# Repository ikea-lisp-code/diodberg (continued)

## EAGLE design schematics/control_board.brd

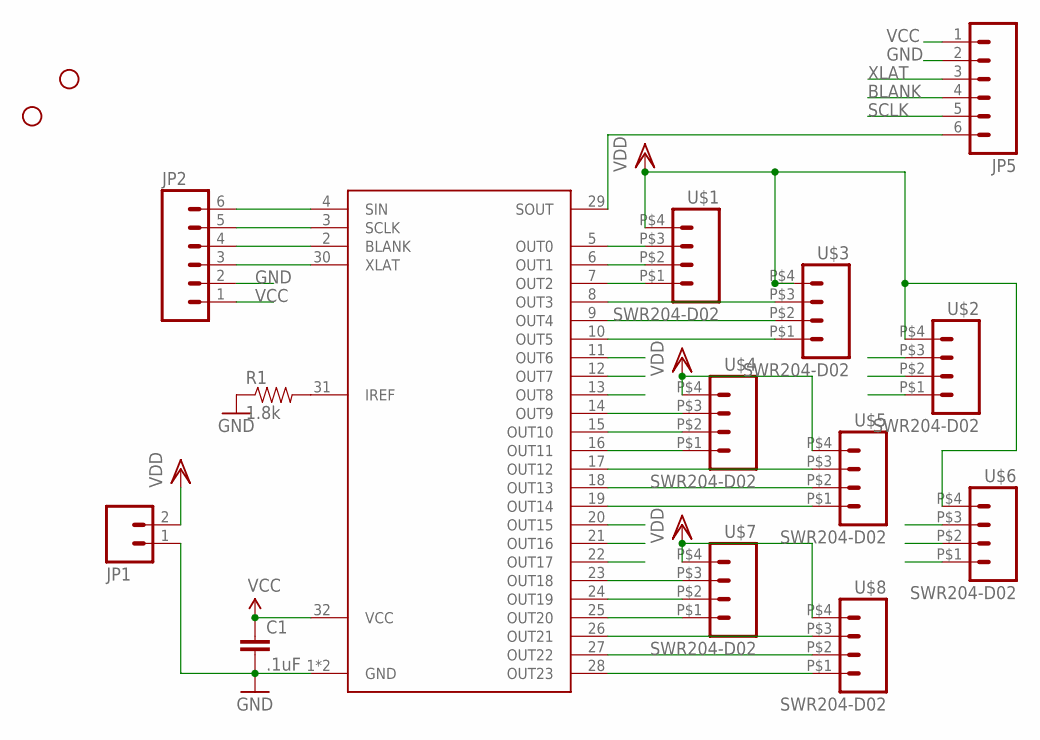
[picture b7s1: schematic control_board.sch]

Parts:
C1: .1uF; 0603-CAP
JP1: M02-JST-2MM-SMT; JST-2-SMD
JP2, JP5: M06LOCK; 1X06_LOCK
R1: 1.8k; 0603-RES
STANDOFF2, STANDOFF3: STAND-OFF
TLC5947: TLC5947DAP; DAP
U$1, U$2, U$3, U$4, U$5, U$6, U$7, U$8: SWR204-D02; SWR204

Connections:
BLANK: JP2.4, JP5.4, TLC5947.2 (BLANK)
GND: C1.2, JP1.1 (2), JP2.2, JP5.2, R1.1, TLC5947.1 (GND), TLC5947.GND
unnamed: R1.2, TLC5947.31 (IREF)
OUT0: TLC5947.5 (OUT0), U$1.P$3 (3)
OUT1: TLC5947.6 (OUT1), U$1.P$2 (2)
OUT2: TLC5947.7 (OUT2), U$1.P$1 (1)
OUT3: TLC5947.8 (OUT3), U$3.P$3 (3)
OUT4: TLC5947.9 (OUT4), U$3.P$2 (2)
OUT5: TLC5947.10 (OUT5), U$3.P$1 (1)
OUT6: TLC5947.11 (OUT6), U$2.P$3 (3)
OUT7: TLC5947.12 (OUT7), U$2.P$2 (2)
OUT8: TLC5947.13 (OUT8), U$2.P$1 (1)
OUT9: TLC5947.14 (OUT9), U$4.P$3 (3)
OUT10: TLC5947.15 (OUT10), U$4.P$2 (2)
OUT11: TLC5947.16 (OUT11), U$4.P$1 (1)
OUT12: TLC5947.17 (OUT12), U$5.P$3 (3)
OUT13: TLC5947.18 (OUT13), U$5.P$2 (2)
OUT14: TLC5947.19 (OUT14), U$5.P$1 (1)
OUT15: TLC5947.20 (OUT15), U$6.P$3 (3)
OUT16: TLC5947.21 (OUT16), U$6.P$2 (2)
OUT17: TLC5947.22 (OUT17), U$6.P$1 (1)
OUT18: TLC5947.23 (OUT18), U$7.P$3 (3)
OUT19: TLC5947.24 (OUT19), U$7.P$2 (2)
OUT20: TLC5947.25 (OUT20), U$7.P$1 (1)
OUT21: TLC5947.26 (OUT21), U$8.P$3 (3)
OUT22: TLC5947.27 (OUT22), U$8.P$2 (2)
OUT23: TLC5947.28 (OUT23), U$8.P$1 (1)
SCLK: JP2.5, JP5.5, TLC5947.3 (SCLK)
SIN: JP2.6, TLC5947.4 (SIN)
SOUT: JP5.6, TLC5947.29 (SOUT)
VCC: C1.1, JP2.1, JP5.1, TLC5947.32 (VCC)
VDD: JP1.2 (1), U$1.P$4 (4), U$2.P$4 (4), U$3.P$4 (4), U$4.P$4 (4), U$5.P$4 (4), U$6.P$4 (4), U$7.P$4 (4), U$8.P$4 (4)
XLAT: JP2.3, JP5.3, TLC5947.30 (XLAT)

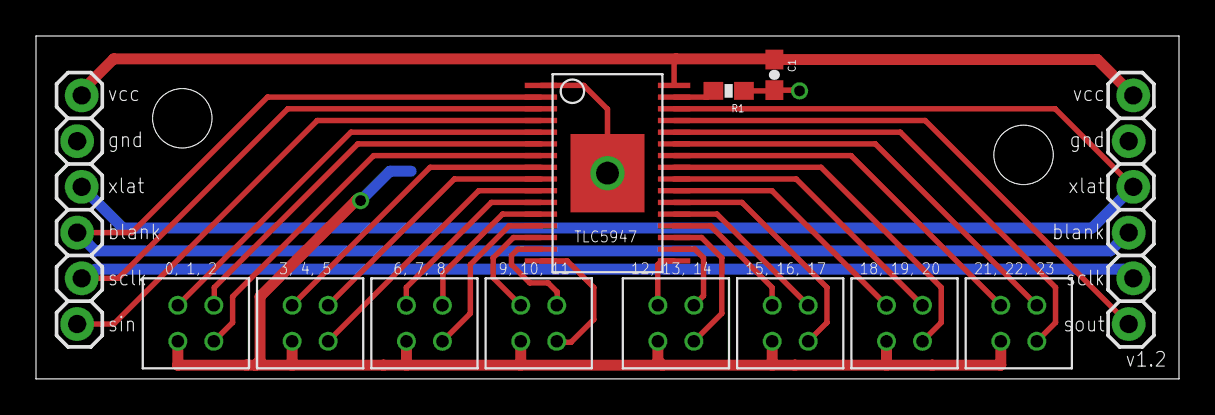
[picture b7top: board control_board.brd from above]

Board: 2 copper layers, 63.5 x 19.1 mm, 16 parts (1 on the bottom side), 33 nets.

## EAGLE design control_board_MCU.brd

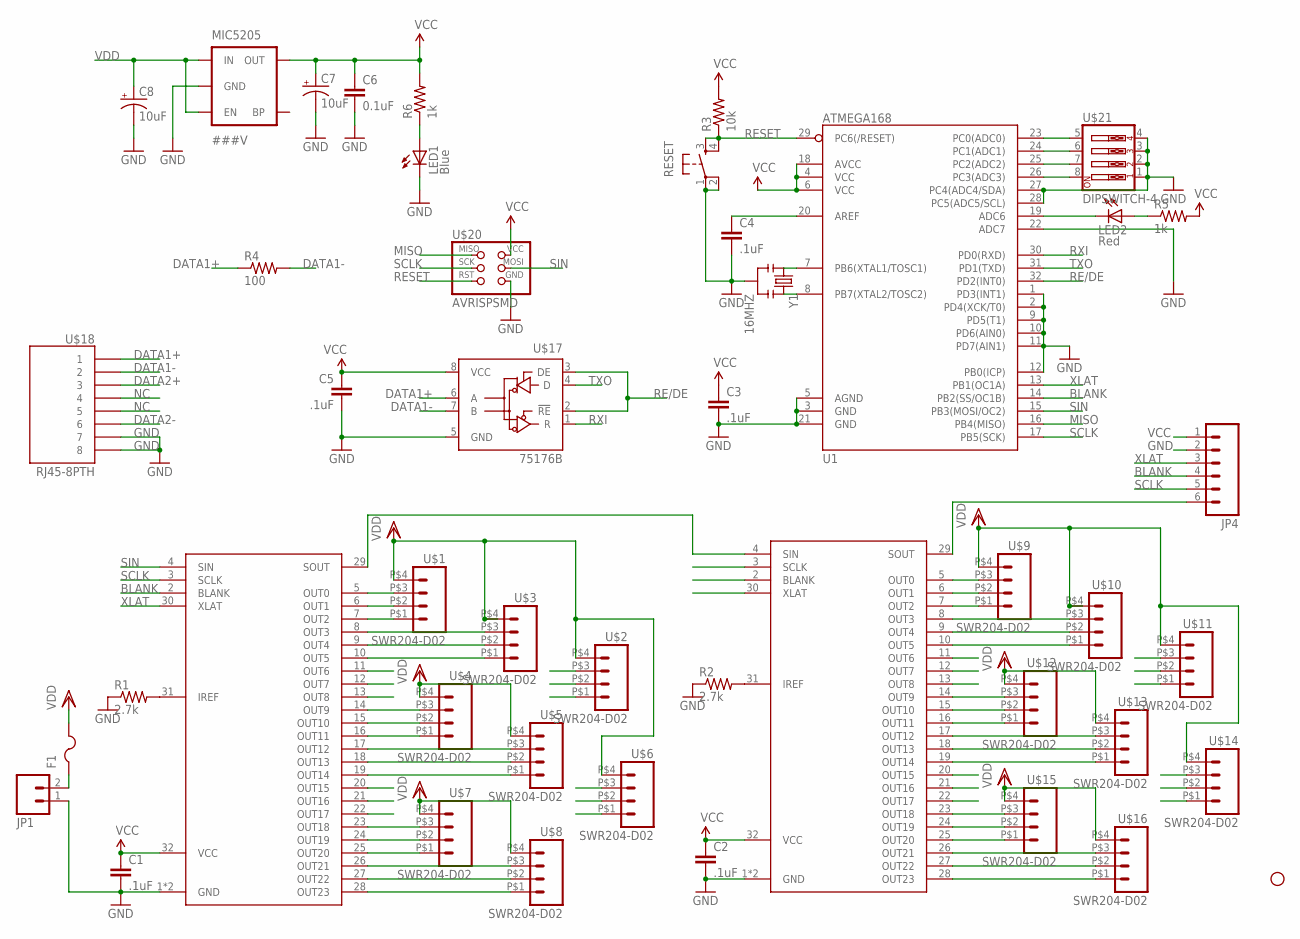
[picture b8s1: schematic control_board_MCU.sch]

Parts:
C1, C2, C3, C4, C5: .1uF; 0402-CAP
C6: 0.1uF; 0402-CAP
C7, C8: 10uF; EIA3216
F1: PTCFUSE-1812; 1812
JP1: M02-JST-2MM-SMT; JST-2-SMD
JP4: M06LOCK; 1X06_LOCK
LED1: Blue; LED-0603
LED2: Red; LED-0603
MIC5205: ###V; SOT23-5
R1, R2: 2.7k; 0603-RES
R3: 10k; 0402-RES
R4: 100; 1206
R5, R6: 1k; C0402
RESET: TAC_SWITCHSMD; TACTILE_SWITCH_SMD
STANDOFF1: STAND-OFF
TLC5947, TLC5947-2: TLC5947DAP; DAP
U1: ATMEGA168; TQFP32-08
U$1, U$2, U$3, U$4, U$5, U$6, U$7, U$8, U$9, U$10, U$11, U$12, U$13, U$14, U$15, U$16: SWR204-D02; SWR204
U$17: 75176B; D_R-PDSO-G8
U$18: RJ45-8PTH; RJ45-8
U$20: AVRISPSMD; 2X03SMD
U$21: DIPSWITCH-4; DIPSWITCH-04
Y1: 16MHZ; RESONATOR-SMD

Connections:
BLANK: JP4.4, TLC5947.2 (BLANK), TLC5947-2.2 (BLANK), U1.14 (PB2(SS/OC1B))
DATA1+: R4.1, U$17.6 (A), U$18.1
DATA1-: R4.2, U$17.7 (B), U$18.2
DATA2+: U$18.3
DATA2-: U$18.6
GND: C1.2, C2.2, C3.2, C4.2, C5.2, C6.2, C7.C (-), C8.C (-), JP1.1 (2), JP4.2, LED1.C, MIC5205.2 (GND), R1.1, R2.1, RESET.1, RESET.2, TLC5947.1 (GND), TLC5947.GND, TLC5947-2.1 (GND), TLC5947-2.GND, U1.1 (PD3(INT1)), U1.2 (PD4(XCK/T0)), U1.3 (GND), U1.5 (AGND), U1.9 (PD5(T1)), U1.10 (PD6(AIN0)), U1.11 (PD7(AIN1)), U1.12 (PB0(ICP)), U1.21 (GND), U1.22 (ADC7), U1.27 (PC4(ADC4/SDA)), U1.28 (PC5(ADC5/SCL)), U$17.5 (GND), U$18.7, U$18.8, U$20.6 (GND), U$21.1, U$21.2, U$21.3, U$21.4, Y1.2
MISO: U1.16 (PB4(MISO)), U$20.1 (MISO)
unnamed: R1.2, TLC5947.31 (IREF)
unnamed: R2.2, TLC5947-2.31 (IREF)
unnamed: C4.1, U1.20 (AREF)
unnamed: U1.7 (PB6(XTAL1/TOSC1)), Y1.1
unnamed: U1.8 (PB7(XTAL2/TOSC2)), Y1.3
unnamed: LED2.C, U1.19 (ADC6)
unnamed: LED2.A, R5.1
unnamed: F1.1, JP1.2 (1)
unnamed: U1.23 (PC0(ADC0)), U$21.5
unnamed: U1.24 (PC1(ADC1)), U$21.6
unnamed: U1.25 (PC2(ADC2)), U$21.7
unnamed: U1.26 (PC3(ADC3)), U$21.8
unnamed: LED1.A, R6.1
NC: U$18.4, U$18.5
OUT0: TLC5947.5 (OUT0), U$1.P$3 (3)
OUT1: TLC5947.6 (OUT1), U$1.P$2 (2)
OUT2: TLC5947.7 (OUT2), U$1.P$1 (1)
OUT3: TLC5947.8 (OUT3), U$3.P$3 (3)
OUT4: TLC5947.9 (OUT4), U$3.P$2 (2)
OUT5: TLC5947.10 (OUT5), U$3.P$1 (1)
OUT6: TLC5947.11 (OUT6), U$2.P$3 (3)
OUT7: TLC5947.12 (OUT7), U$2.P$2 (2)
OUT8: TLC5947.13 (OUT8), U$2.P$1 (1)
OUT9: TLC5947.14 (OUT9), U$4.P$3 (3)
OUT10: TLC5947.15 (OUT10), U$4.P$2 (2)
OUT11: TLC5947.16 (OUT11), U$4.P$1 (1)
OUT12: TLC5947.17 (OUT12), U$5.P$3 (3)
OUT13: TLC5947.18 (OUT13), U$5.P$2 (2)
OUT14: TLC5947.19 (OUT14), U$5.P$1 (1)
OUT15: TLC5947.20 (OUT15), U$6.P$3 (3)
OUT16: TLC5947.21 (OUT16), U$6.P$2 (2)
OUT17: TLC5947.22 (OUT17), U$6.P$1 (1)
OUT18: TLC5947.23 (OUT18), U$7.P$3 (3)
OUT19: TLC5947.24 (OUT19), U$7.P$2 (2)
OUT20: TLC5947.25 (OUT20), U$7.P$1 (1)
OUT21: TLC5947.26 (OUT21), U$8.P$3 (3)
OUT22: TLC5947.27 (OUT22), U$8.P$2 (2)
OUT23: TLC5947.28 (OUT23), U$8.P$1 (1)
OUT24: TLC5947-2.5 (OUT0), U$9.P$3 (3)
OUT25: TLC5947-2.6 (OUT1), U$9.P$2 (2)
OUT26: TLC5947-2.7 (OUT2), U$9.P$1 (1)
OUT27: TLC5947-2.8 (OUT3), U$10.P$3 (3)
OUT28: TLC5947-2.9 (OUT4), U$10.P$2 (2)
OUT29: TLC5947-2.10 (OUT5), U$10.P$1 (1)
OUT30: TLC5947-2.11 (OUT6), U$11.P$3 (3)
OUT31: TLC5947-2.12 (OUT7), U$11.P$2 (2)
OUT32: TLC5947-2.13 (OUT8), U$11.P$1 (1)
OUT33: TLC5947-2.14 (OUT9), U$12.P$3 (3)
OUT34: TLC5947-2.15 (OUT10), U$12.P$2 (2)
OUT35: TLC5947-2.16 (OUT11), U$12.P$1 (1)
OUT36: TLC5947-2.17 (OUT12), U$13.P$3 (3)
OUT37: TLC5947-2.18 (OUT13), U$13.P$2 (2)
OUT38: TLC5947-2.19 (OUT14), U$13.P$1 (1)
OUT39: TLC5947-2.20 (OUT15), U$14.P$3 (3)
OUT40: TLC5947-2.21 (OUT16), U$14.P$2 (2)
OUT41: TLC5947-2.22 (OUT17), U$14.P$1 (1)
OUT42: TLC5947-2.23 (OUT18), U$15.P$3 (3)
OUT43: TLC5947-2.24 (OUT19), U$15.P$2 (2)
OUT44: TLC5947-2.25 (OUT20), U$15.P$1 (1)
OUT45: TLC5947-2.26 (OUT21), U$16.P$3 (3)
OUT46: TLC5947-2.27 (OUT22), U$16.P$2 (2)
OUT47: TLC5947-2.28 (OUT23), U$16.P$1 (1)
RE/DE: U1.32 (PD2(INT0)), U$17.2 (!RE), U$17.3 (DE)
RESET: R3.1, RESET.3, RESET.4, U1.29 (PC6(/RESET)), U$20.5 (RST)
RXI: U1.30 (PD0(RXD)), U$17.1 (R)
SCLK: JP4.5, TLC5947.3 (SCLK), TLC5947-2.3 (SCLK), U1.17 (PB5(SCK)), U$20.3 (SCK)
SIN: TLC5947.4 (SIN), U1.15 (PB3(MOSI/OC2)), U$20.4 (MOSI)
SOUT: TLC5947.29 (SOUT), TLC5947-2.4 (SIN)
SOUT1: JP4.6, TLC5947-2.29 (SOUT)
TXO: U1.31 (PD1(TXD)), U$17.4 (D)
VCC: C1.1, C2.1, C3.1, C5.1, C6.1, C7.A (+), JP4.1, MIC5205.5 (OUT), R3.2, R5.2, R6.2, TLC5947.32 (VCC), TLC5947-2.32 (VCC), U1.4 (VCC), U1.6 (VCC), U1.18 (AVCC), U$17.8 (VCC), U$20.2 (VCC)
VDD: C8.A (+), F1.2, MIC5205.1 (IN), MIC5205.3 (EN), U$1.P$4 (4), U$2.P$4 (4), U$3.P$4 (4), U$4.P$4 (4), U$5.P$4 (4), U$6.P$4 (4), U$7.P$4 (4), U$8.P$4 (4), U$9.P$4 (4), U$10.P$4 (4), U$11.P$4 (4), U$12.P$4 (4), U$13.P$4 (4), U$14.P$4 (4), U$15.P$4 (4), U$16.P$4 (4)
XLAT: JP4.3, TLC5947.30 (XLAT), TLC5947-2.30 (XLAT), U1.13 (PB1(OC1A))

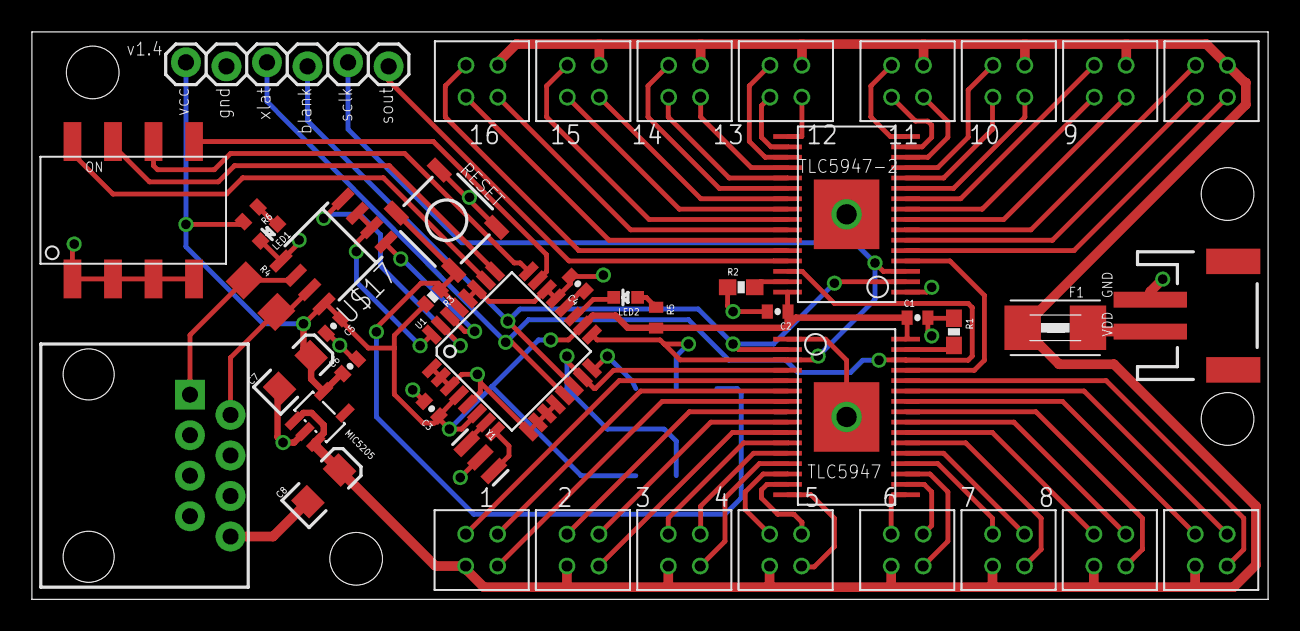
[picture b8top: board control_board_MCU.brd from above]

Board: 2 copper layers, 77.5 x 35.6 mm, 49 parts (1 on the bottom side), 78 nets.

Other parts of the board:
STANDOFF2, STANDOFF3, STANDOFF4: STAND-OFF

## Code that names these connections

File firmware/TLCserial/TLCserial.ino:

#include <DMXSerial.h>

/*
    Basic Pin setup:
    ------------                                  ---u----
    ARDUINO   13|-> SCLK (pin 25)           OUT1 |1     28| OUT channel 0
              12|                           OUT2 |2     27|-> GND (VPRG)
              11|-> SIN (pin 26)            OUT3 |3     26|-> SIN (pin 11)
              10|-> BLANK (pin 23)          OUT4 |4     25|-> SCLK (pin 13)
               9|-> XLAT (pin 24)             .  |5     24|-> XLAT (pin 9)
               8|                             .  |6     23|-> BLANK (pin 10)
               7|                             .  |7     22|-> GND
               6|                             .  |8     21|-> VCC (+5V)
               5|                             .  |9     20|-> 2K Resistor -> GND
               4|                             .  |10    19|-> +5V (DCPRG)
               3|-> GSCLK (pin 18)            .  |11    18|-> GSCLK (pin 3)
               2|                             .  |12    17|-> SOUT
               1|                             .  |13    16|-> XERR
               0|                           OUT14|14    15| OUT channel 15
    ------------                                  --------

    -  Put the longer leg (anode) of the LEDs in the +5V and the shorter leg
         (cathode) in OUT(0-15).
    -  +5V from Arduino -> TLC pin 21 and 19     (VCC and DCPRG)
    -  GND from Arduino -> TLC pin 22 and 27     (GND and VPRG)
    -  digital 3        -> TLC pin 18            (GSCLK)
    -  digital 9        -> TLC pin 24            (XLAT)
    -  digital 10       -> TLC pin 23            (BLANK)
    -  digital 11       -> TLC pin 26            (SIN)
    -  digital 13       -> TLC pin 25            (SCLK)
    -  The 2K resistor between TLC pin 20 and GND will let ~20mA through each
       LED.  To be precise, it's I = 39.06 / R (in ohms).  This doesn't depend
       on the LED driving voltage.
    - (Optional): put a pull-up resistor (~10k) between +5V and BLANK so that
                  all the LEDs will turn off when the Arduino is reset.

    If you are daisy-chaining more than one TLC, connect the SOUT of the first
    TLC to the SIN of the next.  All the other pins should just be connected
    together:
        BLANK on Arduino -> BLANK of TLC1 -> BLANK of TLC2 -> ...
        XLAT on Arduino  -> XLAT of TLC1  -> XLAT of TLC2  -> ...
    The one exception is that each TLC needs it's own resistor between pin 20
    and GND.

    This library uses the PWM output ability of digital pins 3, 9, 10, and 11.
    Do not use analogWrite(...) on these pins.

    This sketch does the Knight Rider strobe across a line of LEDs.

    Alex Leone <acleone ~AT~ gmail.com>, 2009-02-03 */

#include "Tlc5940.h"
#define NUM_LEDS 16

static int bright[3] = {0, 1224, 2650};
boolean demo_mode = false;
uint_fast16_t dmx_address;

void setup()
{
  /* Call Tlc.init() to setup the tlc.
     You can optionally pass an initial PWM value (0 - 4095) for all channels.*/
  Tlc.init();
  Tlc.set(0, 4095);
  Tlc.update();
  delay(500);
  
  // Configure the DIP switch pins to have pullups
  PORTC |= (1 << 0) + (1 << 1) + (1 << 2) + (1 << 3);
  
  // Set the differential transceiver to receive mode.
  digitalWrite(2, LOW);
  pinMode(2, OUTPUT);
  
  // Setup the DMX interrupts / parsing code.
  DMXSerial.init(DMXReceiver);
  Tlc.set(1, 4095);
  Tlc.update();
  delay(500);
  
  // Get the preset dmx address from DIP switch
  dmx_address = PINC & 0x0F;
  dmx_address = dmx_address ^ 0x0F;
  // Check for demo mode.
  if (dmx_address > 10) {
    demo_mode = true;
  }
  
  // Chill out.
  delay(500);
  Tlc.set(2, 4095);
  Tlc.update();
}

void loop()
{
   if (!demo_mode) {
     for (uint_fast16_t i = 0; i < 48; i++) {
       Tlc.set(i, DMXSerial.read(i + 1 + dmx_address*NUM_LEDS*3) << 4);
     }

   }
   else {
     demo_mode_lights();
   }
}

void demo_mode_lights() {
  uint16_t bright = 1024;
  uint16_t del = 100;
  
  if (dmx_address == 0x0E) {
    for (uint_fast16_t i = 0; i < 48; i++) {
       Tlc.set(i, bright);
     }
     Tlc.update();
     return;
  }
  
  for (int i = 0; i < 9; i++) {
    Tlc.set(i*3, bright);
  }
  Tlc.update();
  delay(del);
  
  for (int i = 0; i < 9; i++) {
    Tlc.set(i*3+2, 0);
  }
  Tlc.update();
  delay(del);
  
  for (int i = 0; i < 9; i++) {
    Tlc.set(i*3+1, bright);
  }
  Tlc.update();
  delay(del);
  
  for (int i = 0; i < 9; i++) {
    Tlc.set(i*3, 0);
  }
  Tlc.update();
  delay(del);
  
  for (int i = 0; i < 9; i++) {
    Tlc.set(i*3+2, bright);
  }
  Tlc.update();
  delay(del);
  
  for (int i = 0; i < 9; i++) {
    Tlc.set(i*3+1, 0);
  }
  Tlc.update();
  delay(del);
}

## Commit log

2013-05-08 boards
2013-05-09 deleted pogo pin board
2013-05-17 minor edits
    - changed RGB board hole to 7/16"
    - minor edits to MCU board
2013-05-17 .gitignore
2013-05-17 .gitignore update
2013-05-17 delete
2013-05-21 Initial commit: directory structure, ola client (C++/Python client interface), readme's, example plugin.
2013-05-21 Removed startinstance.py
2013-05-29 PyGameRenderer and miscellaneous improvements: testing utilities, bug fixes, comments.
2013-05-29 Removed old setup.py cruft.
2013-05-30 Fixed package hierarchy, added manifest, tested module importing, fixed some stupid mistakes.
2013-05-31 pylint bugfixes. Test renderer works using the pygame renderer.
2013-05-31 RGB <--> HSB pixel color conversions.
2013-05-31 Fucking shitcock.
2013-06-01 Some working examples of user applications.
2013-06-01 Various bug fixes to diodberg.core
2013-06-04 RaspberryPi renderer for direct PWM GPIO and serial GPIO to WS2812.
2013-06-04 new things!
2013-06-04 DMX over serial renderer for the RaspberryPi.
2013-06-04 Bug fixes for last commit for Pi DMX-over-serial class and test.
2013-06-04 Proper DMX serial configuration....maybe.
2013-06-04 Goodbye, OLA.
2013-06-04 Very simple test routine for testing DMX over serial protocol.
2013-06-04 Bug fix in last commit.
2013-06-04 Exposed write on DMX serial renderer.
2013-06-04 attiny2313 control board
2013-06-04 minor edit to attiny board
2013-06-05 Adding initial firmware.
2013-06-05 Updated README.
2013-06-05 Oh sweet RaspberryPi, you whisper such sweet nothings in my ear, like _250kilobaud? Your wish is my command._ LIES. POISON. PySerialRender is now patched to run at pyserial's max clock.
2013-06-05 Arduino, whyyyyyyy?
2013-06-06 Broke renderers out into separate files, added some performance improvements.
2013-06-06 Patch.
2013-06-06 I am apparently sleeping today, Christ.
2013-06-06 added anti-spinning technology
2013-06-06 gitignore eagle temp files
2013-06-06 More optimizations, refactoring (removed redundant datatypes), and fixed executable bug.
2013-06-06 Updates to README and distutils.
2013-06-06 add readme
2013-06-06 Added copyright license.
2013-06-09 Moved python into python/ directory.
2013-06-09 Added num_pixels parameter to serial renderer executable and fixed random_panel() to assign DMX addresses.
2013-06-10 Fix.
2013-06-16 Added a few firmware comments.
2013-06-16 Adding alternate driver architecture.
2013-06-29 Combine DMX and demo mode for WS2811 LED driver boards.
2013-06-29 Convert TLC driver board code to use DMX address and have a demo mode.
2013-07-14 changed WS2812 controller to uUSB, minor spacing edits to everything else
2013-07-15 added full ethernet switch board (unfinished), modified WS2812 controller
2013-07-20 minor tweaks
2013-07-25 Made DMX splitter board for RPi -> other boards. iff --git a/schematics/dmx_splitter.brd b/schematics/dmx_splitter.brd new file mode 100644 index 0000000..f48532d --- /dev/null +++ b/schematics/dmx_s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
2013-07-26 made board 10cm wide
2013-07-26 Remove negative offset on board edge...
2013-08-02 Added an in-terminal, curses-based renderer; web front-end and initialization routine; LICENSE; core type for Routes.
2013-08-02 Added data configuration file. Merging in changes and pushing into a temporarily broken state.
2013-08-02 Added numba autojit to core types to speed up evaluation. Running codebase with these optimizations requires Anaconda Python (from ContinuumIO), but are only used if the numba package is available.
2013-08-02 Moved ConditionalDecorator into utils.
2013-08-03 Aubio-based utility for doing sound input.
2013-08-03 squash
2013-08-03 Clean up frimware demo modes.
    Make there be three demo modes: color fade, color flash, white.
2013-08-12 Numpy changes and profiling.
2013-08-12 Updated README to reflect python-only changes.
